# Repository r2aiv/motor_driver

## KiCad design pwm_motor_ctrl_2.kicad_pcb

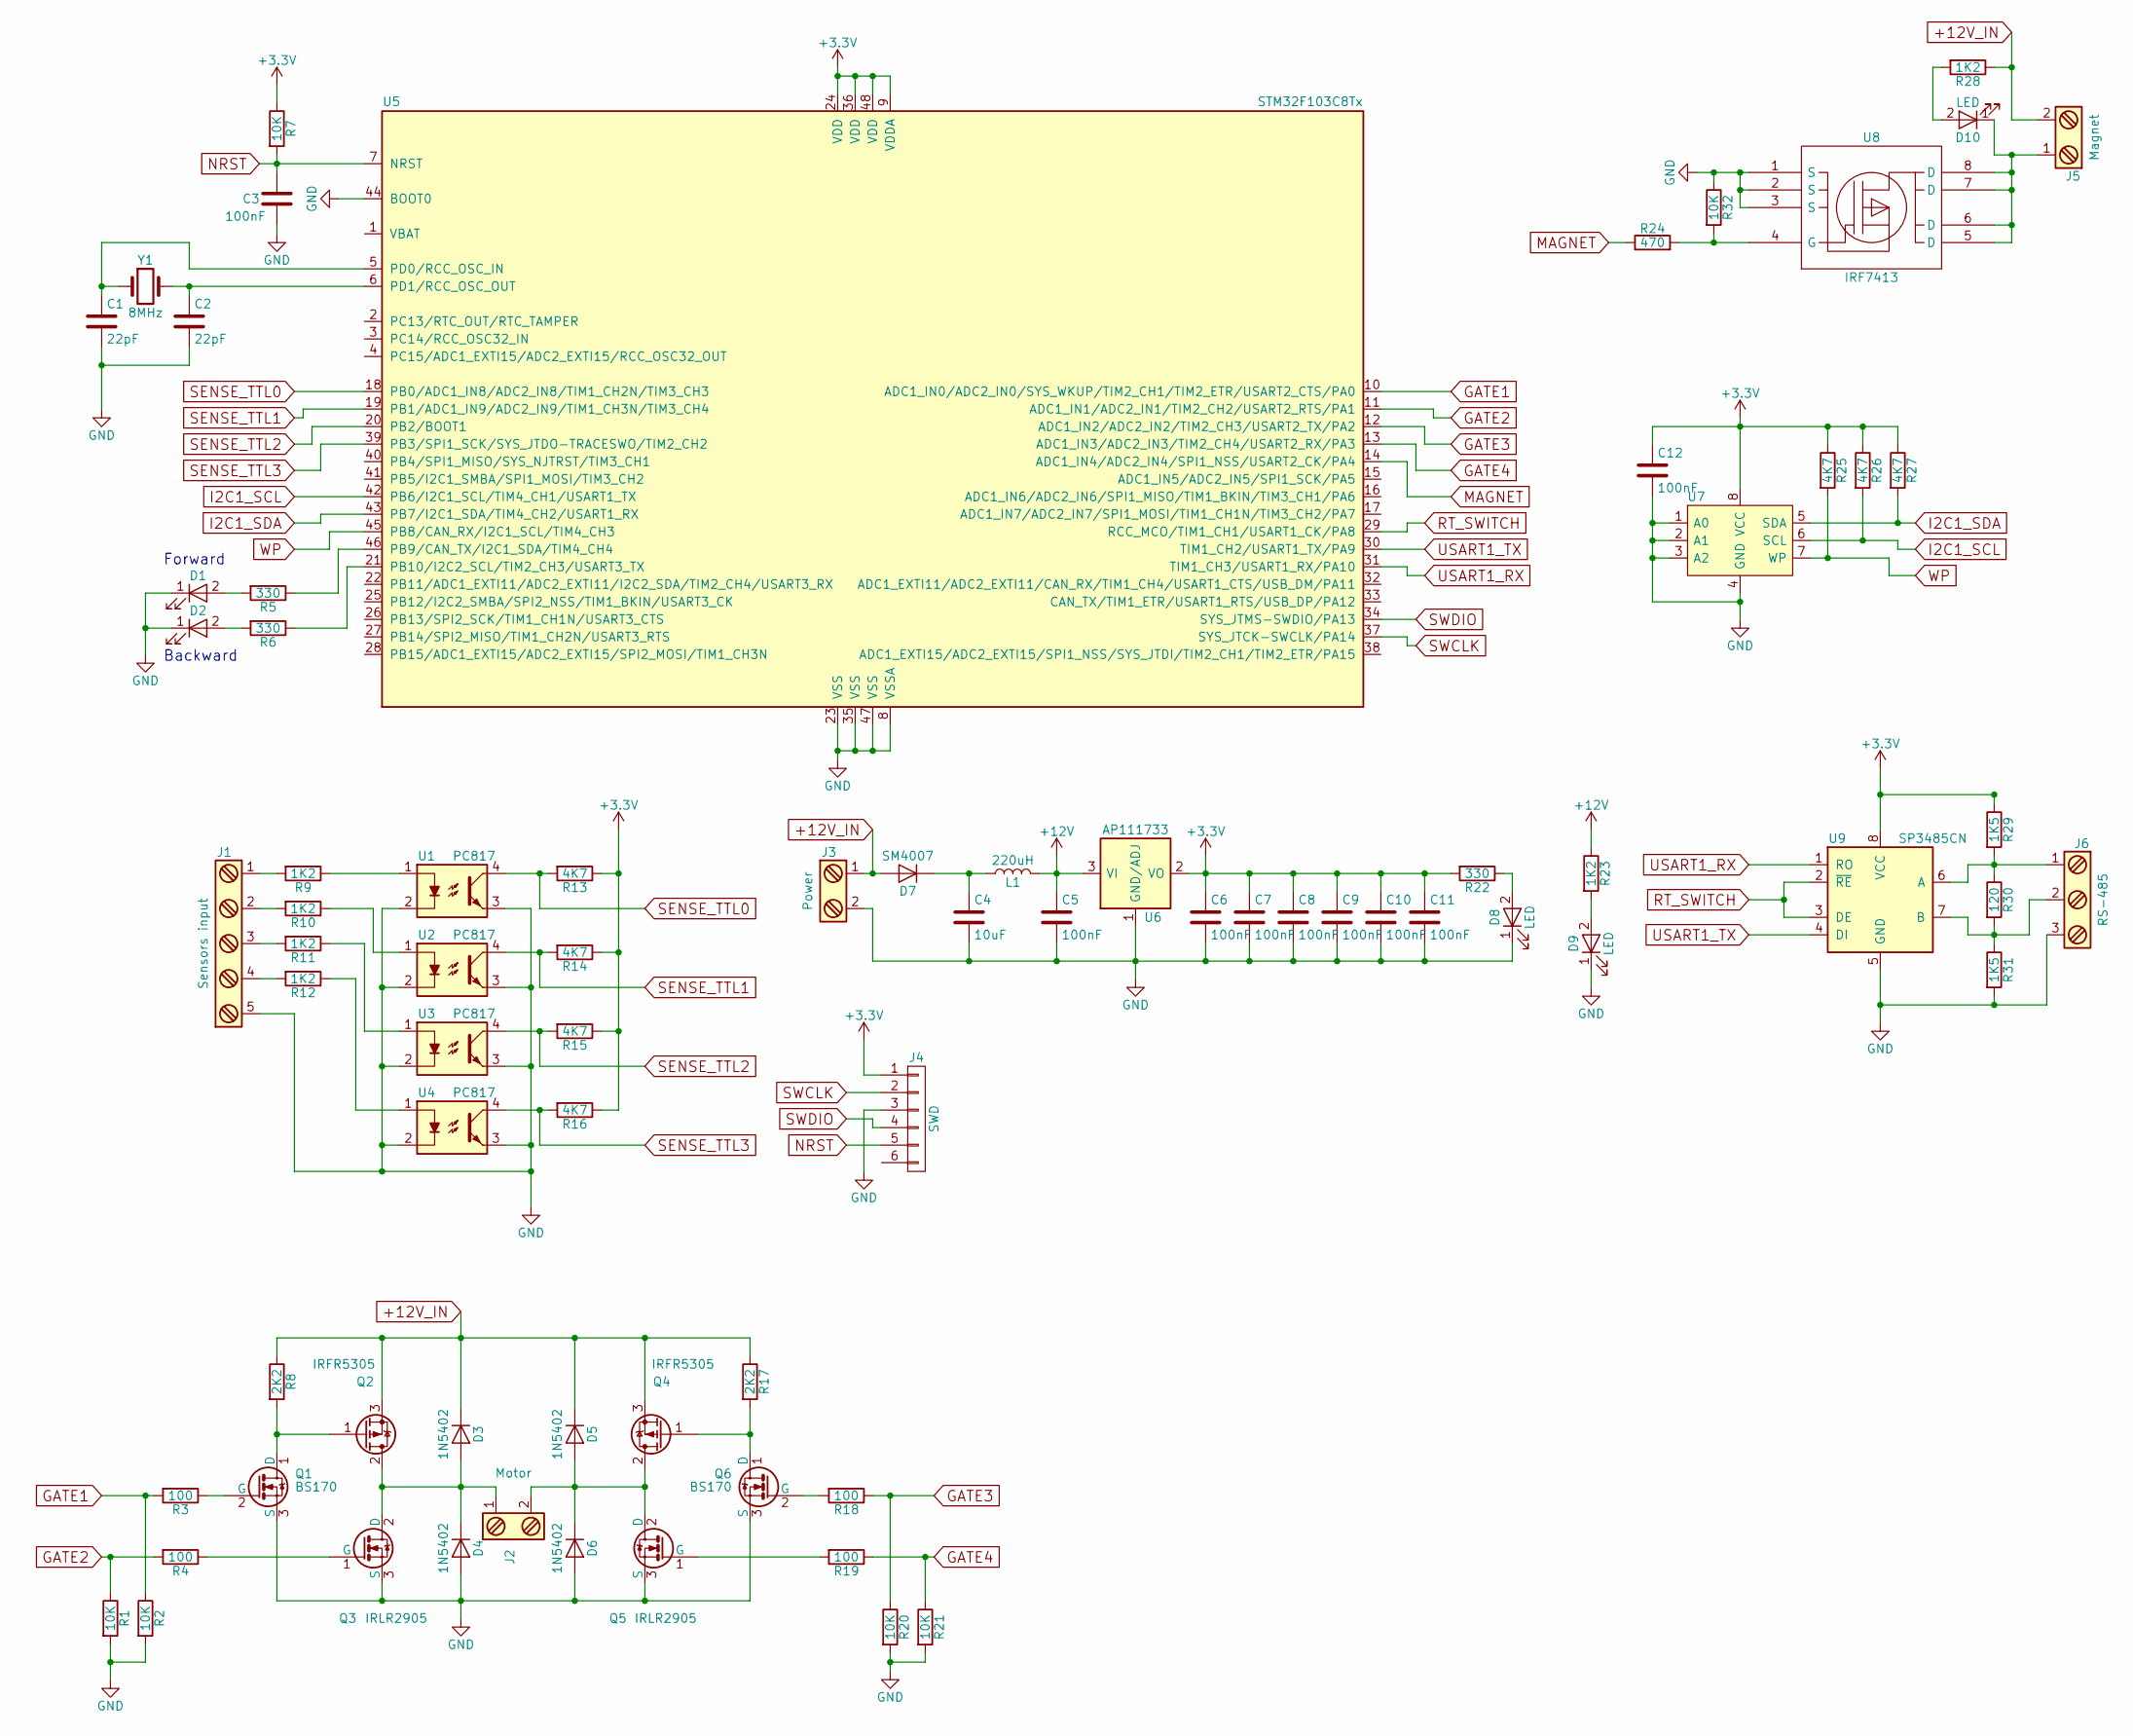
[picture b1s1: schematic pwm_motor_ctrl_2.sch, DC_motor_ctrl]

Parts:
C1, C2: 22pF; C_0805_HandSoldering
C3, C5, C6, C7, C8, C9, C10, C11, C12: 100nF; C_0805_HandSoldering
C4: 10uF; C_0805_HandSoldering
D1, D2, D8, D9, D10: LED; LED_0805
D3, D4, D5, D6: 1N5402; D_DO-201AD_P12.70mm_Horizontal
D7: SM4007; D_MELF
J1: Sensors input; bornier5
J2: Motor; bornier2
J3: Power; bornier2
J4: SWD; Pin_Header_Straight_1x06_Pitch2.54mm
J5: Magnet; bornier2
J6: RS-485; bornier3
L1: 220uH; Choke_SMD_12x12mm_h6mm
Q1, Q6: BS170; TO-92_Molded_Narrow
Q2, Q4: IRFR5305; TO-252-2_Rectifier
Q3, Q5: IRLR2905; TO-252-2_Rectifier
R1, R2, R7, R20, R21, R32: 10K; R_0805_HandSoldering
R3, R4, R18, R19: 100; R_0805_HandSoldering
R5, R6, R22: 330; R_0805_HandSoldering
R8, R17: 2K2; R_0805_HandSoldering
R9, R10, R11, R12, R23, R28: 1K2; R_0805_HandSoldering
R13, R14, R15, R16, R25, R26, R27: 4K7; R_0805_HandSoldering
R24: 470; R_0805_HandSoldering
R29, R31: 1K5; R_0805_HandSoldering
R30: 120; R_0805_HandSoldering
U1, U2, U3, U4: PC817; DIP-4_W7.62mm_SMD
U5: STM32F103C8Tx; LQFP-48_7x7mm_Pitch0.5mm
U6: AP111733; SOT-223
U7: 24LC02; SOIC-8_3.9x4.9mm_Pitch1.27mm
U8: IRF7413; SOIC-8_3.9x4.9mm_Pitch1.27mm
U9: SP3485CN; SOIC-8_3.9x4.9mm_Pitch1.27mm
Y1: 8MHz; Crystal_HC49-U_Vertical

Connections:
+3V3: C6.1, C7.1, C8.1, C9.1, C10.1, C11.1, C12.1, J4.1, R7.1, R13.1, R14.1, R15.1, R16.1, R22.2, R25.1, R26.1, R27.1, R29.1, U5.9 (VDDA), U5.24 (VDD), U5.36 (VDD), U5.48 (VDD), U6.2 (VO), U6.4 (VO), U7.8 (VCC), U9.8 (VCC)
+12V: C5.1, L1.2, R23.1, U6.3 (VI)
+12V_IN: D3.1 (K), D5.1 (K), D7.2 (A), J3.1, J5.2, Q2.3 (S), Q4.3 (S), R8.1, R17.1, R28.1
GATE1: R2.1, R3.2, U5.10 (ADC1_IN0/ADC2_IN0/SYS_WKUP/TIM2_CH1/TIM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)
GATE2: R1.1, R4.2, U5.11 (ADC1_IN1/ADC2_IN1/TIM2_CH2/USART2_RTS/P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)
GATE3: R18.1, R20.1, U5.12 (ADC1_IN2/ADC2_IN2/TIM2_CH3/USART2_TX/PA2)
GATE4: R19.1, R21.1, U5.13 (ADC1_IN3/ADC2_IN3/TIM2_CH4/USART2_RX/PA3)
GND: C1.2, C2.2, C3.2, C4.2, C5.2, C6.2, C7.2, C8.2, C9.2, C10.2, C11.2, C12.2, D1.1 (K), D2.1 (K), D4.2 (A), D6.2 (A), D8.1 (K), D9.1 (K), J1.5, J3.2, J4.3, J6.3, Q1.3 (S), Q3.3 (S), Q5.3 (S), Q6.3 (S), R1.2, R2.2, R20.2, R21.2, R31.2, R32.1, U1.2, U1.3, U2.2, U2.3, U3.2, U3.3, U4.2, U4.3, U5.8 (VSSA), U5.23 (VSS), U5.35 (VSS), U5.44 (BOOT0), U5.47 (VSS), U6.1 (GND/ADJ), U7.1 (A0), U7.2 (A1), U7.3 (A2), U7.4 (GND), U8.1 (S), U8.2 (S), U8.3 (S), U9.5 (GND)
I2C1_SCL: R26.2, U5.42 (PB6/I2C1_SCL/TIM4_CH1/USART1_TX), U7.6 (SCL)
I2C1_SDA: R27.2, U5.43 (PB7/I2C1_SDA/TIM4_CH2/USART1_RX), U7.5 (SDA)
MAGNET: R24.1, U5.14 (ADC1_IN4/ADC2_IN4/SPI1_NSS/USART2_CK/PA4)
NRST: C3.1, J4.5, R7.2, U5.7 (NRST)
unnamed: C1.1, U5.5 (PD0/RCC_OSC_IN), Y1.1
unnamed: C2.1, U5.6 (PD1/RCC_OSC_OUT), Y1.2
unnamed: C4.1, D7.1 (K), L1.1
unnamed: D1.2 (A), R5.2
unnamed: D2.2 (A), R6.2
unnamed: D3.2 (A), D4.1 (K), J2.1, Q2.2 (D), Q3.2 (D)
unnamed: D5.2 (A), D6.1 (K), J2.2, Q4.2 (D), Q5.2 (D)
unnamed: D8.2 (A), R22.1
unnamed: D9.2 (A), R23.2
unnamed: D10.1 (K), J5.1, U8.5 (D), U8.6 (D), U8.7 (D), U8.8 (D)
unnamed: D10.2 (A), R28.2
unnamed: J1.1, R9.2
unnamed: J1.2, R10.2
unnamed: J1.3, R11.2
unnamed: J1.4, R12.2
unnamed: J6.1, R29.2, R30.1, U9.6 (A)
unnamed: J6.2, R30.2, R31.1, U9.7 (B)
unnamed: Q1.1 (D), Q2.1 (G), R8.2
unnamed: Q1.2 (G), R3.1
unnamed: Q3.1 (G), R4.1
unnamed: Q4.1 (G), Q6.1 (D), R17.2
unnamed: Q5.1 (G), R19.2
unnamed: Q6.2 (G), R18.2
unnamed: R5.1, U5.46 (PB9/CAN_TX/I2C1_SDA/TIM4_CH4)
unnamed: R6.1, U5.21 (PB10/I2C2_SCL/TIM2_CH3/USART3_TX)
unnamed: R9.1, U1.1
unnamed: R10.1, U2.1
unnamed: R11.1, U3.1
unnamed: R12.1, U4.1
unnamed: R24.2, R32.2, U8.4 (G)
RT_SWITCH: U5.29 (RCC_MCO/TIM1_CH1/USART1_CK/PA8), U9.2 (~RE~), U9.3 (DE)
SENSE_TTL0: R13.2, U1.4, U5.18 (PB0/ADC1_IN8/ADC2_IN8/TIM1_CH2N/TIM3_CH3)
SENSE_TTL1: R14.2, U2.4, U5.19 (PB1/ADC1_IN9/ADC2_IN9/TIM1_CH3N/TIM3_CH4)
SENSE_TTL2: R15.2, U3.4, U5.20 (PB2/BOOT1)
SENSE_TTL3: R16.2, U4.4, U5.39 (PB3/SPI1_SCK/SYS_JTDO-TRACESWO/TIM2_CH2)
SWCLK: J4.2, U5.37 (SYS_JTCK-SWCLK/PA14)
SWDIO: J4.4, U5.34 (SYS_JTMS-SWDIO/PA13)
USART1_RX: U5.31 (TIM1_CH3/USART1_RX/PA10), U9.1 (RO)
USART1_TX: U5.30 (TIM1_CH2/USART1_TX/PA9), U9.4 (DI)
WP: R25.2, U5.45 (PB8/CAN_RX/I2C1_SCL/TIM4_CH3), U7.7 (WP)

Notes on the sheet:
Forward
Backward

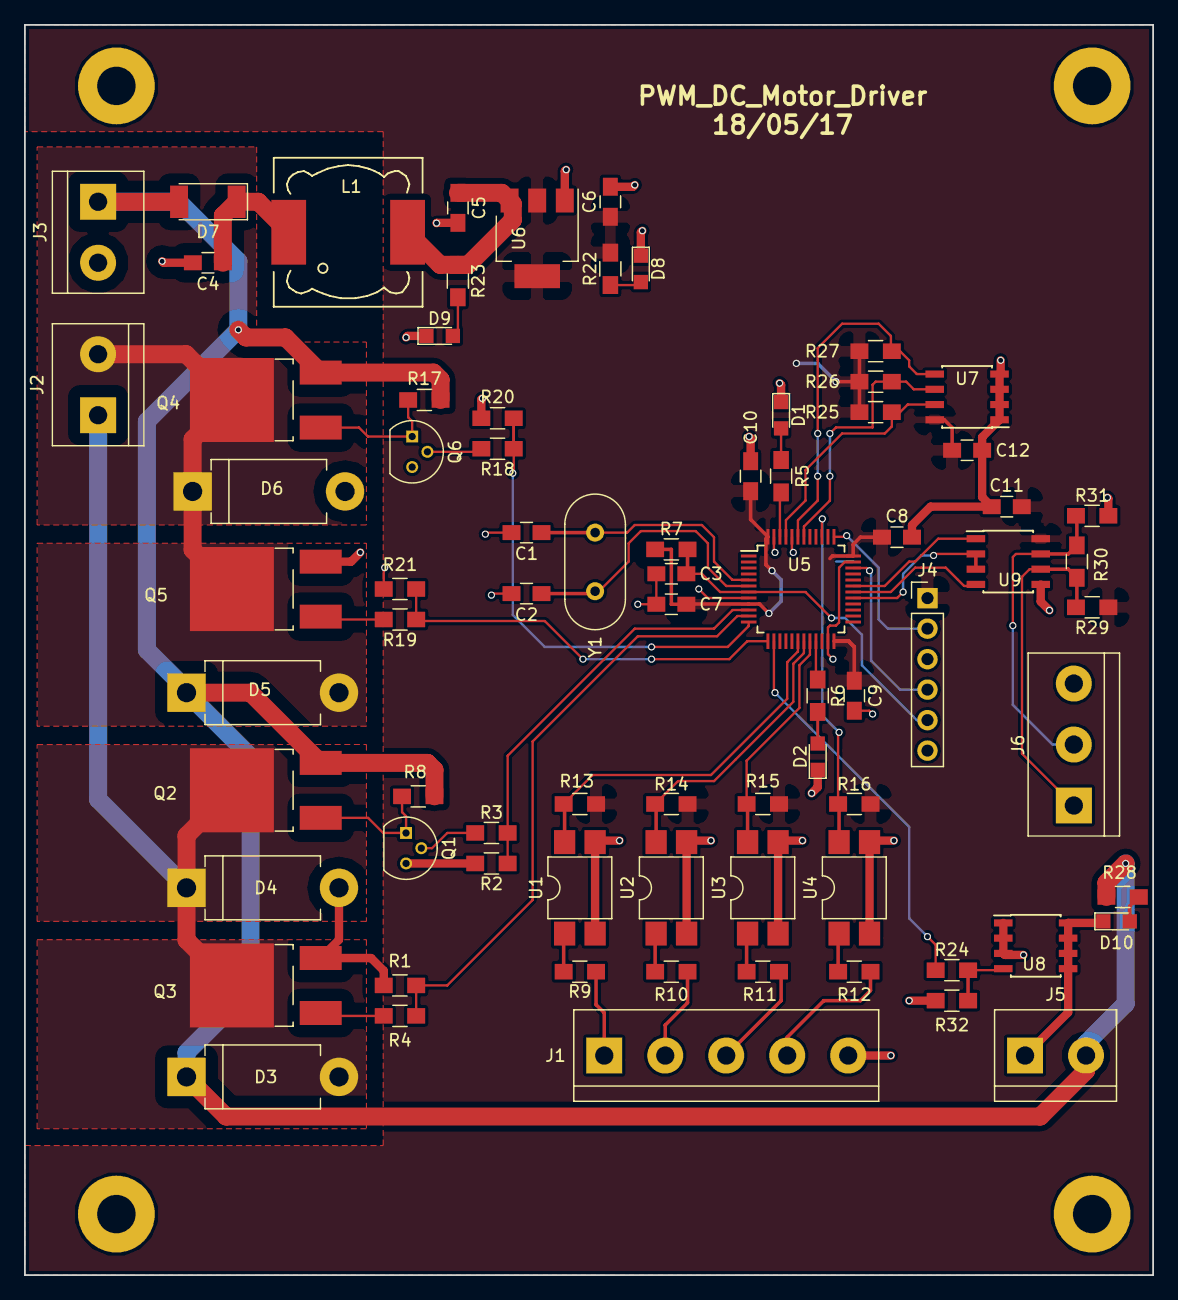
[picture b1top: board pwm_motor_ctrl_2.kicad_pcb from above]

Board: 2 copper layers, 94.0 x 104.1 mm, 77 parts (0 on the bottom side), 52 nets.

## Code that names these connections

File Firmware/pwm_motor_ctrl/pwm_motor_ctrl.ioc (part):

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Mcu.Name=STM32F103C(8-B)Tx
Mcu.Package=LQFP48
Mcu.UserName=STM32F103C8Tx
PA0-WKUP.GPIOParameters=GPIO_Label
PA0-WKUP.GPIO_Label=GATE1
PA0-WKUP.Signal=GPIO_Output
PA1.GPIOParameters=GPIO_Label
PA1.GPIO_Label=GATE2
PA1.Signal=GPIO_Output
PA10.Mode=Asynchronous
PA10.Signal=USART1_RX
PA13.Mode=Serial_Wire
PA13.Signal=SYS_JTMS-SWDIO
PA14.Mode=Serial_Wire
PA14.Signal=SYS_JTCK-SWCLK
PA2.GPIOParameters=GPIO_Label
PA2.GPIO_Label=GATE3
PA2.Signal=GPIO_Output
PA3.GPIOParameters=GPIO_Label
PA3.GPIO_Label=GATE4
PA3.Signal=GPIO_Output
PA4.GPIOParameters=GPIO_Label
PA4.GPIO_Label=MAGNET
PA4.Signal=GPIO_Output
PA8.GPIOParameters=GPIO_Label
PA8.GPIO_Label=RT_SWITCH
PA8.Signal=GPIO_Output
PA9.Mode=Asynchronous
PA9.Signal=USART1_TX
PB0.GPIOParameters=GPIO_Label
PB0.GPIO_Label=SENSE_TTL0
PB0.Signal=GPIO_Input
PB1.GPIOParameters=GPIO_Label
PB1.GPIO_Label=SENSE_TTL1
PB1.Signal=GPIO_Input
PB10.GPIOParameters=GPIO_Label
PB10.GPIO_Label=LED2
PB10.Signal=GPIO_Output
PB2.GPIOParameters=GPIO_Label
PB2.GPIO_Label=SENSE_TTL2
PB2.Signal=GPIO_Input
PB3.GPIOParameters=GPIO_Label
PB3.GPIO_Label=SENSE_TTL3
PB3.Signal=GPIO_Input
PB6.Mode=I2C
PB6.Signal=I2C1_SCL
PB7.Mode=I2C
PB7.Signal=I2C1_SDA
PB8.GPIOParameters=GPIO_Label
PB8.GPIO_Label=WP
PB8.Signal=GPIO_Output
PB9.GPIOParameters=GPIO_Label
PB9.GPIO_Label=LED1
PB9.Signal=GPIO_Output
PD0-OSC_IN.Mode=HSE-External-Oscillator
PD0-OSC_IN.Signal=RCC_OSC_IN
PD1-OSC_OUT.Mode=HSE-External-Oscillator
PD1-OSC_OUT.Signal=RCC_OSC_OUT
board=pwm_motor_ctrl

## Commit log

2017-08-29 initial
2017-08-29 refactor
2017-08-29 softstart
2017-08-29 Almost done!
2017-08-29 fin2
